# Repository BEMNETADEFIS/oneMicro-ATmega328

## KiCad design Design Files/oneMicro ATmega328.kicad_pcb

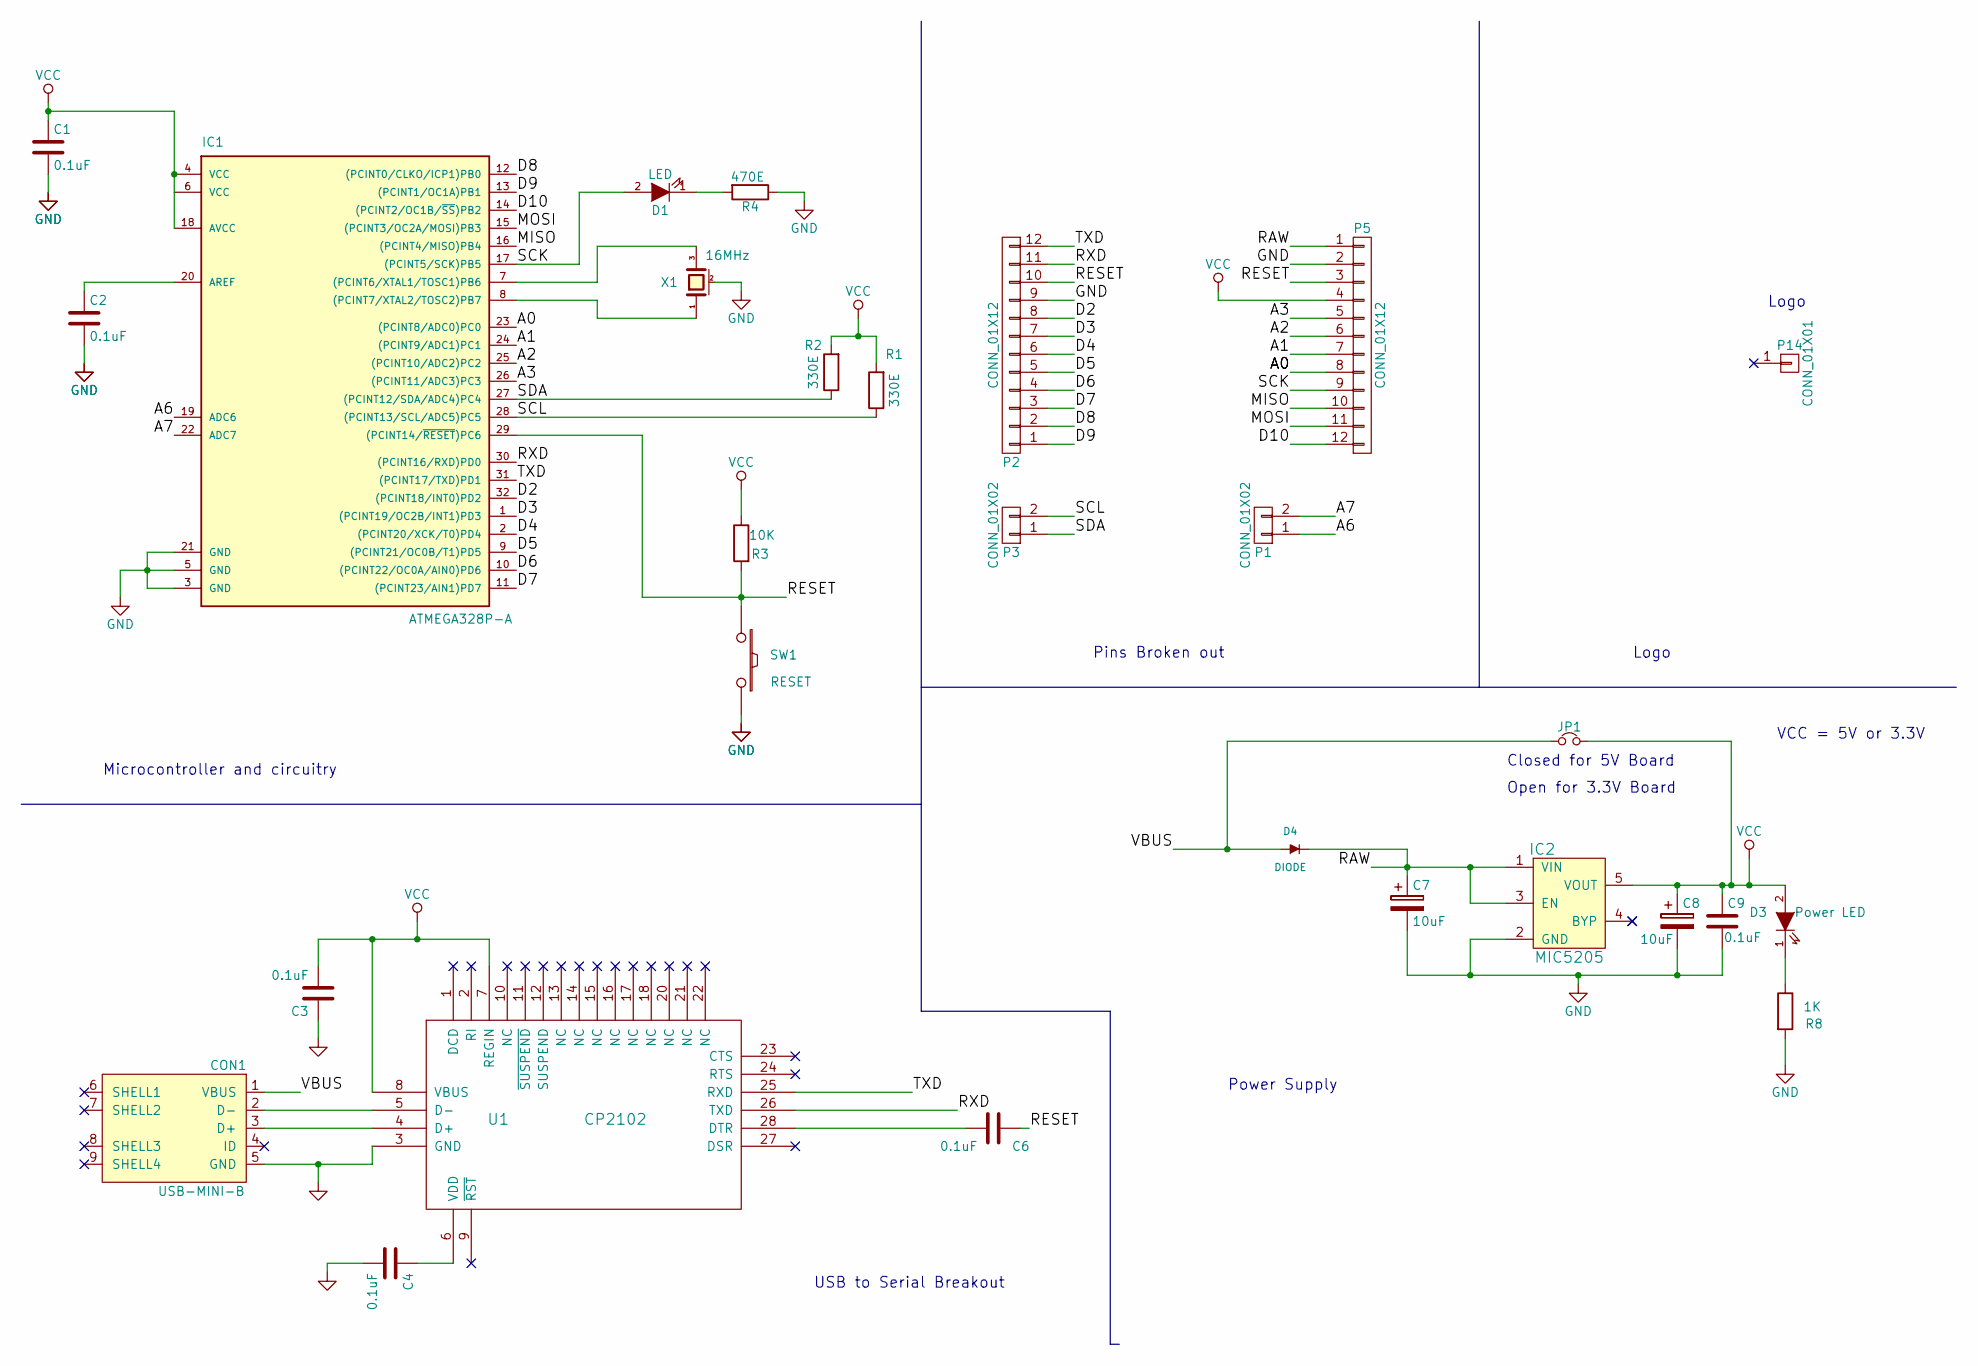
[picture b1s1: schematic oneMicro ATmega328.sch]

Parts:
C1, C2, C3, C4, C6, C9: 0.1uF; C_0603
C7, C8: 10uF; C_1206
CON1: USB-MINI-B; USB_Micro-B_SMD_NEW_1
D1: LED; LED-0603
D3: Power LED; LED-0603
D4: DIODE; Diode_New
IC1: ATMEGA328P-A; LQFP-32_7x7mm_Pitch0.8mm
IC2: MIC5205; SOT-23-5
JP1: Jumper_NC_Small; Pin_Header_Straight_1x02
P1, P3: CONN_01X02; Pin_Header_Straight_1x02
P2, P5: CONN_01X12; Pin_Header_Straight_1x20_New
P14: CONN_01X01; Logo_8
R1, R2: 330E; R_0603
R3: 10K; R_0603
R4: 470E; R_0603
R8: 1K; R_0603
SW1: RESET; smd_push2
U1: CP2102; QFN-28-1EP_5x5mm_Pitch0.5mm
X1: 16MHz; resonator_smd

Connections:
/A0: IC1.23 ((PCINT8/ADC0)PC0), P5.8
/A1: IC1.24 ((PCINT9/ADC1)PC1), P5.7
/A2: IC1.25 ((PCINT10/ADC2)PC2), P5.6
/A3: IC1.26 ((PCINT11/ADC3)PC3), P5.5
/A6: IC1.19 (ADC6), P1.1
/A7: IC1.22 (ADC7), P1.2
/D2: IC1.32 ((PCINT18/INT0)PD2), P2.8
/D3: IC1.1 ((PCINT19/OC2B/INT1)PD3), P2.7
/D4: IC1.2 ((PCINT20/XCK/T0)PD4), P2.6
/D5: IC1.9 ((PCINT21/OC0B/T1)PD5), P2.5
/D6: IC1.10 ((PCINT22/OC0A/AIN0)PD6), P2.4
/D7: IC1.11 ((PCINT23/AIN1)PD7), P2.3
/D8: IC1.12 ((PCINT0/CLKO/ICP1)PB0), P2.2
/D9: IC1.13 ((PCINT1/OC1A)PB1), P2.1
/D10: IC1.14 ((PCINT2/OC1B/~SS~)PB2), P5.12
/MISO: IC1.16 ((PCINT4/MISO)PB4), P5.10
/MOSI: IC1.15 ((PCINT3/OC2A/MOSI)PB3), P5.11
/RAW: C7.1, D4.2 (K), IC2.1 (VIN), IC2.3 (EN), P5.1
/RESET: C6.1, IC1.29 ((PCINT14/~RESET~)PC6), P2.10, P5.3, R3.2, SW1.2
/RXD: IC1.30 ((PCINT16/RXD)PD0), P2.11, U1.26 (TXD)
/SCK: D1.2 (A), IC1.17 ((PCINT5/SCK)PB5), P5.9
/SCL: IC1.28 ((PCINT13/SCL/ADC5)PC5), P3.2, R1.1
/SDA: IC1.27 ((PCINT12/SDA/ADC4)PC4), P3.1, R2.1
/TXD: IC1.31 ((PCINT17/TXD)PD1), P2.12, U1.25 (RXD)
/VBUS: CON1.1 (VBUS), D4.1 (A), JP1.1
GND: C1.2, C2.2, C3.1, C4.2, C7.2, C8.2, C9.2, CON1.5 (GND), IC1.3 (GND), IC1.5 (GND), IC1.21 (GND), IC2.2 (GND), P2.9, P5.2, R4.1, R8.2, SW1.1, U1.3 (GND), X1.2 (case)
unnamed: C2.1, IC1.20 (AREF)
unnamed: C4.1, U1.6 (VDD)
unnamed: C6.2, U1.28 (DTR)
unnamed: CON1.2 (D-), U1.5 (D-)
unnamed: CON1.3 (D+), U1.4 (D+)
unnamed: D1.1 (K), R4.2
unnamed: D3.1 (K), R8.1
unnamed: IC1.7 ((PCINT6/XTAL1/TOSC1)PB6), X1.3 (2)
unnamed: IC1.8 ((PCINT7/XTAL2/TOSC2)PB7), X1.1
VCC: C1.1, C3.2, C8.1, C9.1, D3.2 (A), IC1.4 (VCC), IC1.18 (AVCC), IC2.5 (VOUT), JP1.2, P5.4, R1.2, R2.2, R3.1, U1.7 (REGIN), U1.8 (VBUS)

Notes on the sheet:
USB to Serial Breakout
Logo
Power Supply
Microcontroller and circuitry
Pins Broken out
Logo
Closed for 5V Board
Open for 3.3V Board
VCC = 5V or 3.3V

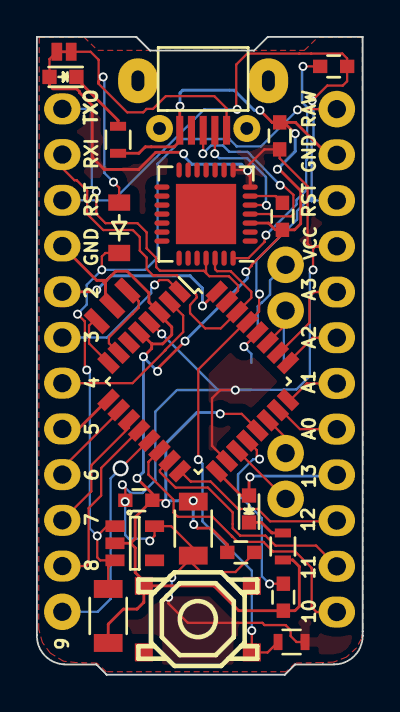
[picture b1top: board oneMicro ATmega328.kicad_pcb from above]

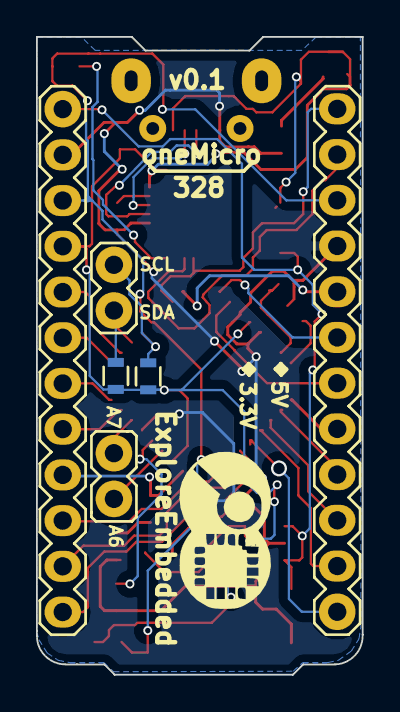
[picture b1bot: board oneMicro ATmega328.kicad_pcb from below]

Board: 2 copper layers, 18.1 x 35.4 mm, 28 parts (5 on the bottom side), 36 nets.

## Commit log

2016-09-24 Design Files added
2016-09-28 Design Completed
2016-09-29 changes in silk and layout
2016-09-29 D13 LED has modified
2016-09-29 Board outline modified
2016-09-29 Gerber file generated
2016-10-01 Exception data cleared
2017-03-17 Changes Done
2017-07-11 BOM generated
